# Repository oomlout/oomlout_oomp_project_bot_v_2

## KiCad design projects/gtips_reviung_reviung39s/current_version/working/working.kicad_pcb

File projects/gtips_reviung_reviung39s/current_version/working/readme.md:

# reviung
 
## summary 
* id: gtips_reviung_reviung39s
* user: gtips
* name: reviung
* board: reviung39s
* repo: https://github.com/gtips/reviung
* src_file_repo_kicad_pcb: reviung39s/pcb/reviung39s.kicad_pcb
* src_file_repo_kicad_pcb_link: https://github.com/gtips/reviung/tree/master/reviung39s/pcb/reviung39s.kicad_pcb

* src_file_repo_sch: reviung39s/pcb/reviung39s.sch
* src_file_repo_sch_link: https://github.com/gtips/reviung/tree/master/reviung39s/pcb/reviung39s.sch
* full details link: https://github.com/oomlout/oomlout_oomp_project_bot_v_2/tree/main/projects/gtips_reviung_reviung39s/current_version/working  

## schematic  
  
[schematic (pdf)](working_schematic.pdf) 

## pcb  

[board (pdf)](working.pdf)  

## working_bom
| Id | Designator | Footprint | Quantity | Designation | Supplier and ref |  | None | 
| --- | --- | --- | --- | --- | --- | --- | --- | 
| 1 | U1 | ProMicro | 1 | ProMicro |  |  | [''] | 
| 2 | D1,D2,D3,D4,D5,D6,D7,D8,D9,D10,D11,D12,D13,D14,D15,D16,D17,D18,D19,D20,D21,D22,D23,D24,D25,D26,D27,D28,D29,D30,D31,D32,D33,D34,D35,D36,D37,D38,D39 | D3_TH | 39 | D |  |  | [''] | 
| 3 | SW1,SW2,SW3,SW4,SW5,SW6,SW7,SW8,SW9,SW10,SW11,SW12,SW13,SW14,SW15,SW16,SW17,SW18,SW19,SW20,SW21,SW22,SW23,SW24,SW25,SW26,SW27,SW28,SW29,SW30,SW31,SW32,SW33,SW34,SW35,SW36,SW37,SW39 | MXOnly-1U-NoLED | 38 | SW_PUSH |  |  | [''] | 
| 4 | SW38 | MXOnly-2.25U-ReversedStabilizers-NoLED | 1 | SW_2U_PUSH |  |  | [''] | 
| 5 | G*** | REVIUNG39s-FS-logo | 1 | LOGO |  |  | [''] | 
| 6 | RESET1 | ResetSW_1side | 1 | SW_PUSH |  |  | [''] | 
| 7 | J1 | StripLED_1side | 1 | Conn_01x03_Shielded |  |  | [''] | 
| 8 | G*** | REVIUNG39s-B-logo | 1 | LOGO |  |  | [''] | 

## bom_schematic
| Ref | Qnty | Value | Cmp name | Footprint | Description | Vendor | DNP | 
| --- | --- | --- | --- | --- | --- | --- | --- | 
| D1, D2, D3, D4, D5, D6, D7, D8, D9, D10, D11, D12, D13, D14, D15, D16, D17, D18, D19, D20, D21, D22, D23, D24, D25, D26, D27, D28, D29, D30, D31, D32, D33, D34, D35, D36, D37, D38, D39 | 39 | D | D | _reviung-kbd:D3_TH | Diode |  |  | 
| J1 | 1 | Conn_01x03_Shielded | Conn_01x03 | _reviung-kbd:StripLED_1side | Generic connector, single row, 01x03, script generated (kicad-library-utils/schlib/autogen/connector/) |  |  | 
| RESET1 | 1 | SW_PUSH | SW_PUSH-_reviung-kbd | _reviung-kbd:ResetSW_1side |  |  |  | 
| SW1, SW2, SW3, SW4, SW5, SW6, SW7, SW8, SW9, SW10, SW11, SW12, SW13, SW14, SW15, SW16, SW17, SW18, SW19, SW20, SW21, SW22, SW23, SW24, SW25, SW26, SW27, SW28, SW29, SW30, SW31, SW32, SW33, SW34, SW35, SW36, SW37, SW39 | 38 | SW_PUSH | SW_PUSH-_reviung-kbd | _reviung-kbd:MXOnly-1U-NoLED |  |  |  | 
| SW38 | 1 | SW_2U_PUSH | SW_PUSH-_reviung-kbd | _reviung-kbd:MXOnly-2.25U-ReversedStabilizers-NoLED |  |  |  | 
| U1 | 1 | ProMicro | ProMicro-_reviung-kbd | _reviung-kbd:ProMicro |  |  |  |

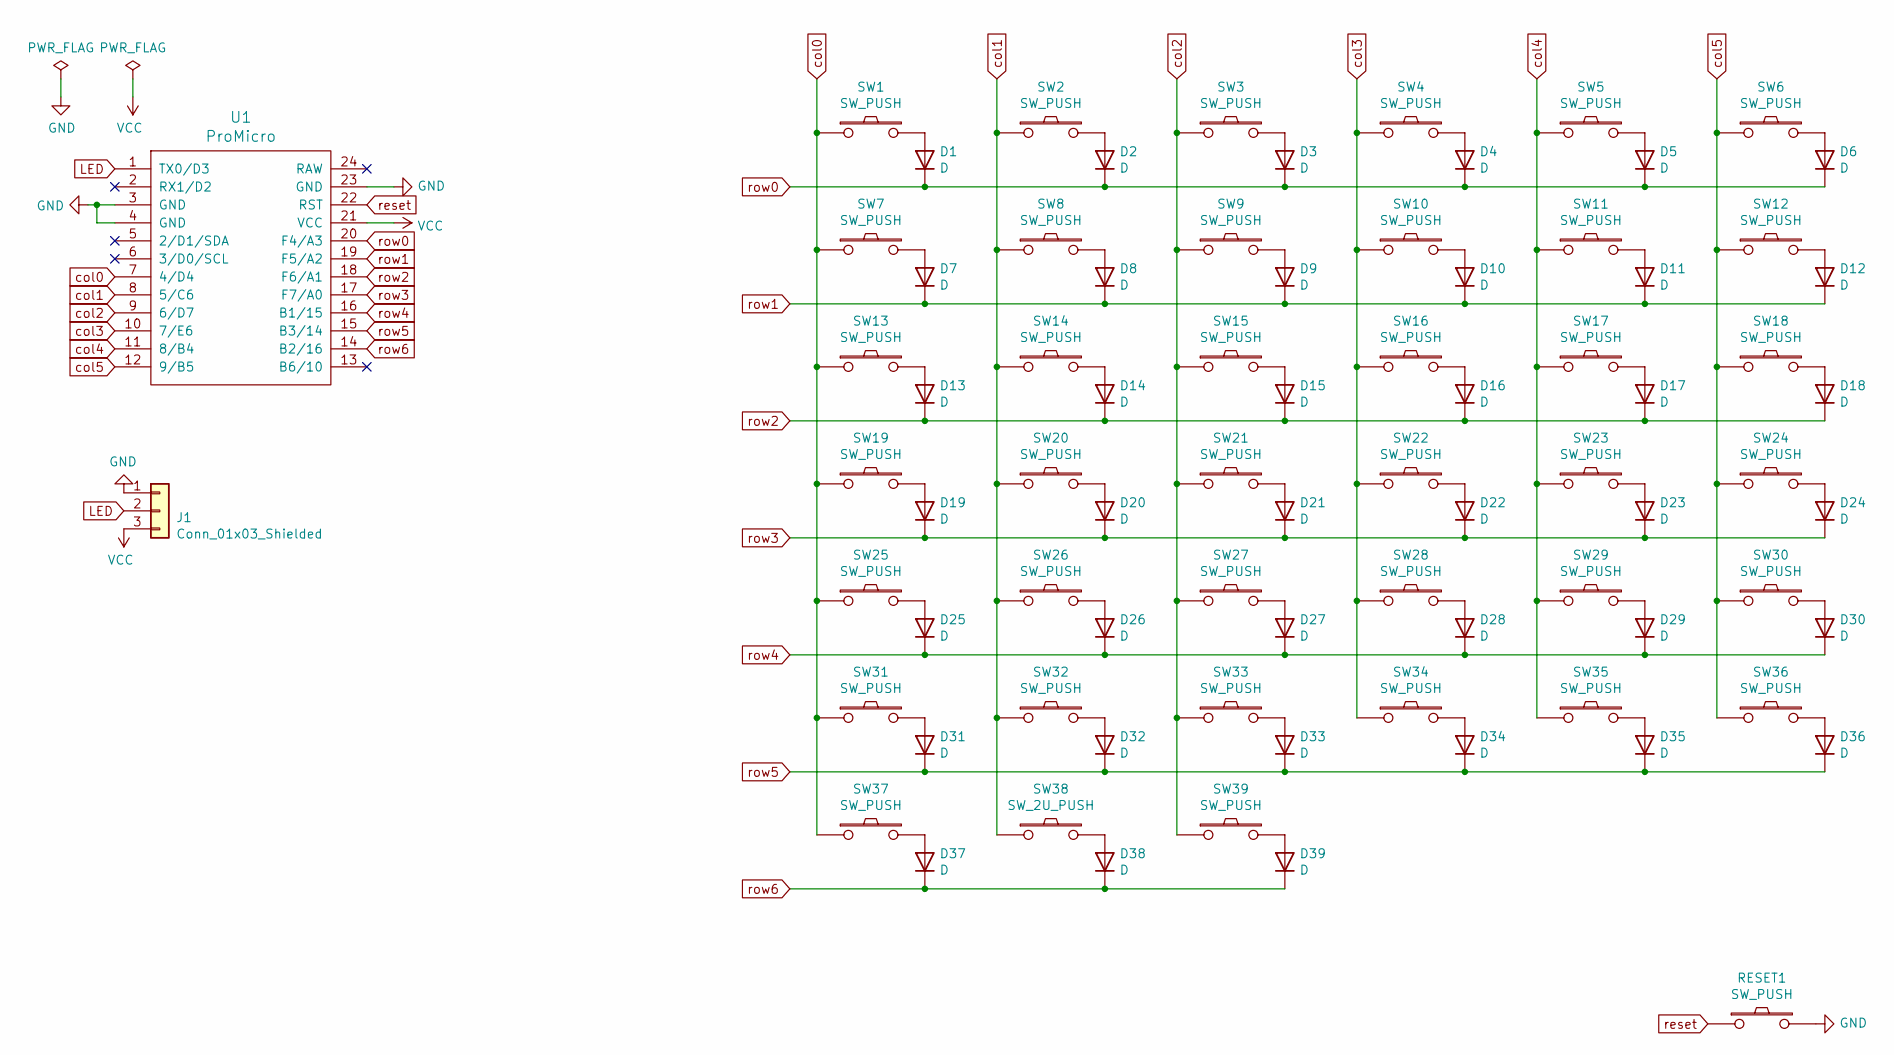
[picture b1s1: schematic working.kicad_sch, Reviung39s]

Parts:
D1, D2, D3, D4, D5, D6, D7, D8, D9, D10, D11, D12, D13, D14, D15, D16, D17, D18, D19, D20, D21, D22, D23, D24, D25, D26, D27, D28, D29, D30, D31, D32, D33, D34, D35, D36, D37, D38, D39: D; D3_TH
J1: Conn_01x03_Shielded; StripLED_1side
RESET1: SW_PUSH; ResetSW_1side
SW1, SW2, SW3, SW4, SW5, SW6, SW7, SW8, SW9, SW10, SW11, SW12, SW13, SW14, SW15, SW16, SW17, SW18, SW19, SW20, SW21, SW22, SW23, SW24, SW25, SW26, SW27, SW28, SW29, SW30, SW31, SW32, SW33, SW34, SW35, SW36, SW37, SW39: SW_PUSH; MXOnly-1U-NoLED
SW38: SW_2U_PUSH; MXOnly-2.25U-ReversedStabilizers-NoLED
U1: ProMicro

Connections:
GND: J1.1, RESET1.2, U1.3 (GND), U1.4 (GND), U1.23 (GND)
LED: J1.2, U1.1 (TX0/D3)
unnamed: D1.2 (A), SW1.2
unnamed: D2.2 (A), SW2.2
unnamed: D3.2 (A), SW3.2
unnamed: D4.2 (A), SW4.2
unnamed: D5.2 (A), SW5.2
unnamed: D6.2 (A), SW6.2
unnamed: D7.2 (A), SW7.2
unnamed: D8.2 (A), SW8.2
unnamed: D9.2 (A), SW9.2
unnamed: D10.2 (A), SW10.2
unnamed: D11.2 (A), SW11.2
unnamed: D12.2 (A), SW12.2
unnamed: D13.2 (A), SW13.2
unnamed: D14.2 (A), SW14.2
unnamed: D15.2 (A), SW15.2
unnamed: D16.2 (A), SW16.2
unnamed: D17.2 (A), SW17.2
unnamed: D18.2 (A), SW18.2
unnamed: D19.2 (A), SW19.2
unnamed: D20.2 (A), SW20.2
unnamed: D21.2 (A), SW21.2
unnamed: D22.2 (A), SW22.2
unnamed: D23.2 (A), SW23.2
unnamed: D24.2 (A), SW24.2
unnamed: D25.2 (A), SW25.2
unnamed: D26.2 (A), SW26.2
unnamed: D27.2 (A), SW27.2
unnamed: D28.2 (A), SW28.2
unnamed: D29.2 (A), SW29.2
unnamed: D30.2 (A), SW30.2
unnamed: D31.2 (A), SW31.2
unnamed: D32.2 (A), SW32.2
unnamed: D33.2 (A), SW33.2
unnamed: D34.2 (A), SW34.2
unnamed: D35.2 (A), SW35.2
unnamed: D36.2 (A), SW36.2
unnamed: D37.2 (A), SW37.2
unnamed: D38.2 (A), SW38.2
unnamed: D39.2 (A), SW39.2
VCC: J1.3, U1.21 (VCC)
col0: SW1.1, SW7.1, SW13.1, SW19.1, SW25.1, SW31.1, SW37.1, U1.7 (4/D4)
col1: SW2.1, SW8.1, SW14.1, SW20.1, SW26.1, SW32.1, SW38.1, U1.8 (5/C6)
col2: SW3.1, SW9.1, SW15.1, SW21.1, SW27.1, SW33.1, SW39.1, U1.9 (6/D7)
col3: SW4.1, SW10.1, SW16.1, SW22.1, SW28.1, SW34.1, U1.10 (7/E6)
col4: SW5.1, SW11.1, SW17.1, SW23.1, SW29.1, SW35.1, U1.11 (8/B4)
col5: SW6.1, SW12.1, SW18.1, SW24.1, SW30.1, SW36.1, U1.12 (9/B5)
reset: RESET1.1, U1.22 (RST)
row0: D1.1 (K), D2.1 (K), D3.1 (K), D4.1 (K), D5.1 (K), D6.1 (K), U1.20 (F4/A3)
row1: D7.1 (K), D8.1 (K), D9.1 (K), D10.1 (K), D11.1 (K), D12.1 (K), U1.19 (F5/A2)
row2: D13.1 (K), D14.1 (K), D15.1 (K), D16.1 (K), D17.1 (K), D18.1 (K), U1.18 (F6/A1)
row3: D19.1 (K), D20.1 (K), D21.1 (K), D22.1 (K), D23.1 (K), D24.1 (K), U1.17 (F7/A0)
row4: D25.1 (K), D26.1 (K), D27.1 (K), D28.1 (K), D29.1 (K), D30.1 (K), U1.16 (B1/15)
row5: D31.1 (K), D32.1 (K), D33.1 (K), D34.1 (K), D35.1 (K), D36.1 (K), U1.15 (B3/14)
row6: D37.1 (K), D38.1 (K), D39.1 (K), U1.14 (B2/16)

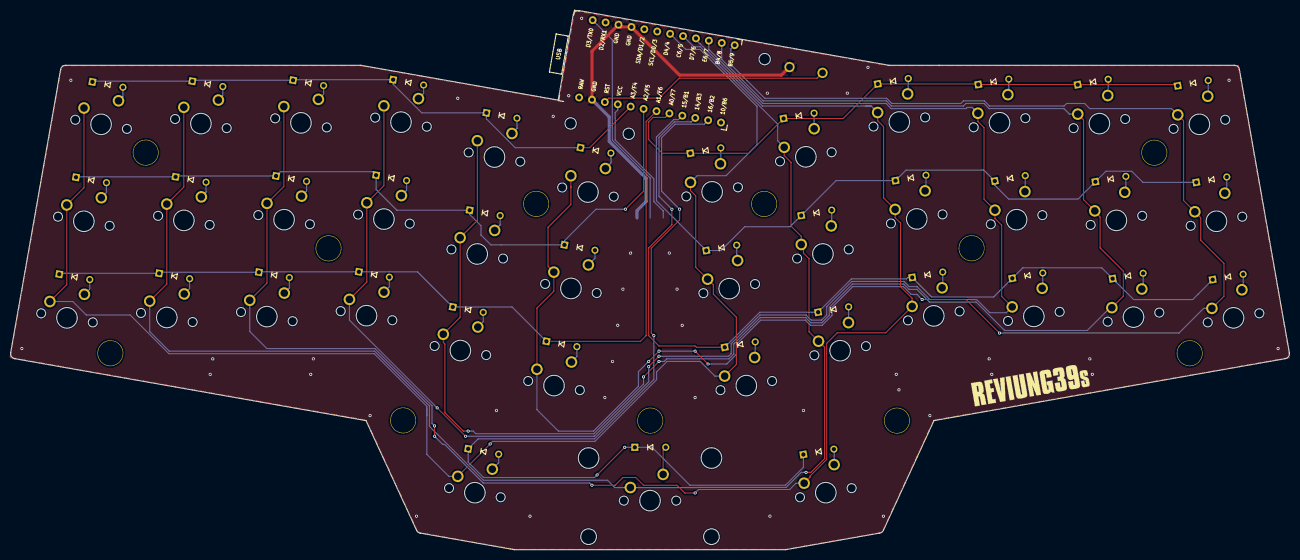
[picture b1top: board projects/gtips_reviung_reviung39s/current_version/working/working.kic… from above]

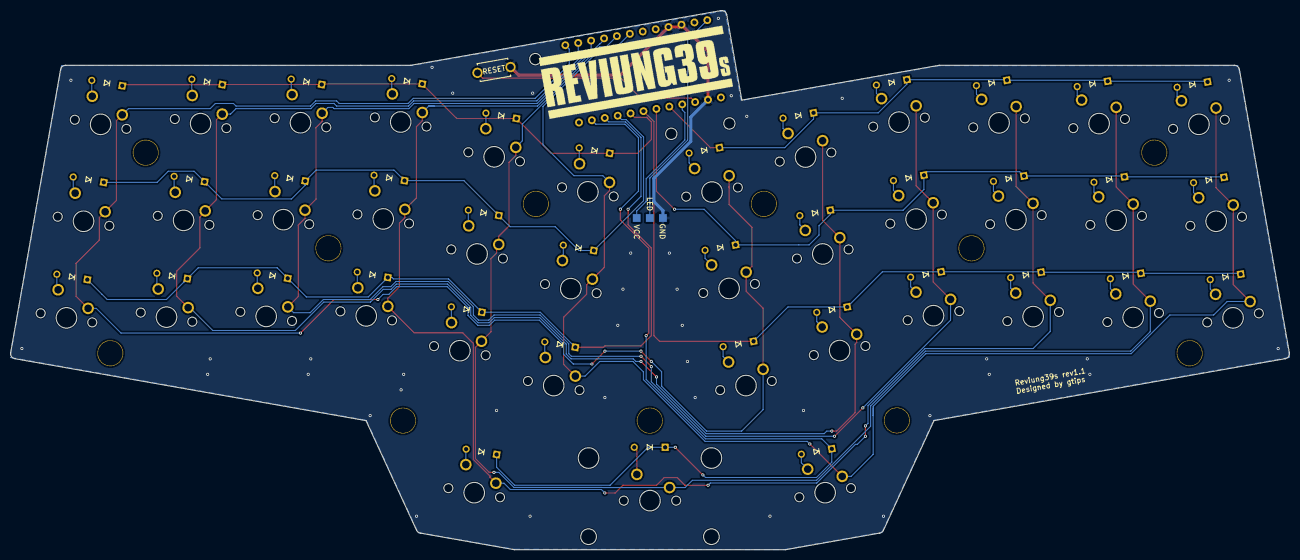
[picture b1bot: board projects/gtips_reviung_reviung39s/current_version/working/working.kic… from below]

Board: 2 copper layers, 247.9 x 104.5 mm, 92 parts (2 on the bottom side), 56 nets.

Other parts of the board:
H1: H1; HOLE
H2: H2; HOLE
H3: H3; HOLE
H4: H4; HOLE
H5: H5; HOLE
H6: H6; HOLE
H7: H7; HOLE
H8: H8; HOLE
H9: H9; HOLE
H10: H10; HOLE
H11: H11; HOLE

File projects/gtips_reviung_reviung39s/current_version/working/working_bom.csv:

"Id";"Designator";"Footprint";"Quantity";"Designation";"Supplier and ref";
1;"U1";"ProMicro";1;"ProMicro";;;
2;"D1,D2,D3,D4,D5,D6,D7,D8,D9,D10,D11,D12,D13,D14,D15,D16,D17,D18,D19,D20,D21,D22,D23,D24,D25,D26,D27,D28,D29,D30,D31,D32,D33,D34,D35,D36,D37,D38,D39";"D3_TH";39;"D";;;
3;"SW1,SW2,SW3,SW4,SW5,SW6,SW7,SW8,SW9,SW10,SW11,SW12,SW13,SW14,SW15,SW16,SW17,SW18,SW19,SW20,SW21,SW22,SW23,SW24,SW25,SW26,SW27,SW28,SW29,SW30,SW31,SW32,SW33,SW34,SW35,SW36,SW37,SW39";"MXOnly-1U-NoLED";38;"SW_PUSH";;;
4;"SW38";"MXOnly-2.25U-ReversedStabilizers-NoLED";1;"SW_2U_PUSH";;;
5;"G***";"REVIUNG39s-FS-logo";1;"LOGO";;;
6;"RESET1";"ResetSW_1side";1;"SW_PUSH";;;
7;"J1";"StripLED_1side";1;"Conn_01x03_Shielded";;;
8;"G***";"REVIUNG39s-B-logo";1;"LOGO";;;

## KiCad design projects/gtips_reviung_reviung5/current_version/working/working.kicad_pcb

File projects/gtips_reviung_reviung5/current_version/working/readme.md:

# reviung
 
## summary 
* id: gtips_reviung_reviung5
* user: gtips
* name: reviung
* board: reviung5
* repo: https://github.com/gtips/reviung
* src_file_repo_kicad_pcb: reviung5/pcb/ver1.0/reviung5.kicad_pcb
* src_file_repo_kicad_pcb_link: https://github.com/gtips/reviung/tree/master/reviung5/pcb/ver1.0/reviung5.kicad_pcb

* src_file_repo_sch: reviung5/pcb/ver1.0/reviung5.sch
* src_file_repo_sch_link: https://github.com/gtips/reviung/tree/master/reviung5/pcb/ver1.0/reviung5.sch
* full details link: https://github.com/oomlout/oomlout_oomp_project_bot_v_2/tree/main/projects/gtips_reviung_reviung5/current_version/working  

## schematic  
  
[schematic (pdf)](working_schematic.pdf) 

## pcb  

[board (pdf)](working.pdf)  

## working_bom
| Id | Designator | Footprint | Quantity | Designation | Supplier and ref |  | None | 
| --- | --- | --- | --- | --- | --- | --- | --- | 
| 1 | RESW1,RESW2 | RotaryEncoder_Alps_EC12E-Switch_Vertical_H20mm_CircularMountingHoles | 2 | Rotary_Encoder_Switch |  |  | [''] | 
| 2 | SW1,SW5 | MXOnly-1U-3pin | 2 | SW_PUSH |  |  | [''] | 
| 3 | SW2,SW3,SW4 | MXOnly-1U-NoLED | 3 | SW_PUSH |  |  | [''] | 
| 4 | U1 | ProMicro | 1 | ProMicro |  |  | [''] | 
| 5 | REF**,REF**,REF** | HOLE_4.2mm | 3 | HOLE_4.2mm |  |  | [''] | 
| 6 | G*** | QMK-x4-ver1 | 1 | LOGO |  |  | [''] | 
| 7 | D1,D2,D3,D4,D5 | D3_TH_SMD_1side | 5 | 1N4148 |  |  | [''] | 
| 8 | reset1 | ResetSW_TH_SMD | 1 | SW_PUSH |  |  | [''] | 
| 9 | RGB1,RGB2,RGB3,RGB4 | LED_WS2812B_PLCC4_5.0x5.0mm_P3.2mm | 4 | WS2812B |  |  | [''] | 
| 10 | G*** | reviung-logo | 1 | LOGO |  |  | [''] | 

## bom_schematic
| Ref | Qnty | Value | Cmp name | Footprint | Description | Vendor | DNP | 
| --- | --- | --- | --- | --- | --- | --- | --- | 
| D1, D2, D3, D4, D5 | 5 | 1N4148 | 1N4148 | _reviung-kbd:D3_TH_SMD_1side | 100V 0.15A standard switching diode, DO-35 |  |  | 
| reset1 | 1 | SW_PUSH | SW_PUSH-_reviung-kbd | _reviung-kbd:ResetSW_TH_SMD |  |  |  | 
| RESW1, RESW2 | 2 | Rotary_Encoder_Switch | Rotary_Encoder_Switch-Device | Rotary_Encoder:RotaryEncoder_Alps_EC12E-Switch_Vertical_H20mm_CircularMountingHoles |  |  |  | 
| RGB1, RGB2, RGB3, RGB4 | 4 | WS2812B | WS2812B | _reviung-kbd:LED_WS2812B_PLCC4_5.0x5.0mm_P3.2mm | RGB LED with integrated controller |  |  | 
| SW1, SW5 | 2 | SW_PUSH | SW_PUSH-_reviung-kbd | _reviung-kbd:MXOnly-1U-3pin |  |  |  | 
| SW2, SW3, SW4 | 3 | SW_PUSH | SW_PUSH-_reviung-kbd | _reviung-kbd:MXOnly-1U-NoLED |  |  |  | 
| U1 | 1 | ProMicro | ProMicro-_reviung-kbd | _reviung-kbd:ProMicro |  |  |  | 

## mounting_holes
| x | y | package | value | ref | size | 
| --- | --- | --- | --- | --- | --- | 
| 0.0 | 0.86 | RotaryEncoder_Alps_EC12E-Switch_Vertical_H20mm_CircularMountingHoles | Rotary_Encoder_Switch | RESW1 | m3 | 
| 78.94 | 0.0 | RotaryEncoder_Alps_EC12E-Switch_Vertical_H20mm_CircularMountingHoles | Rotary_Encoder_Switch | RESW2 | m3 |

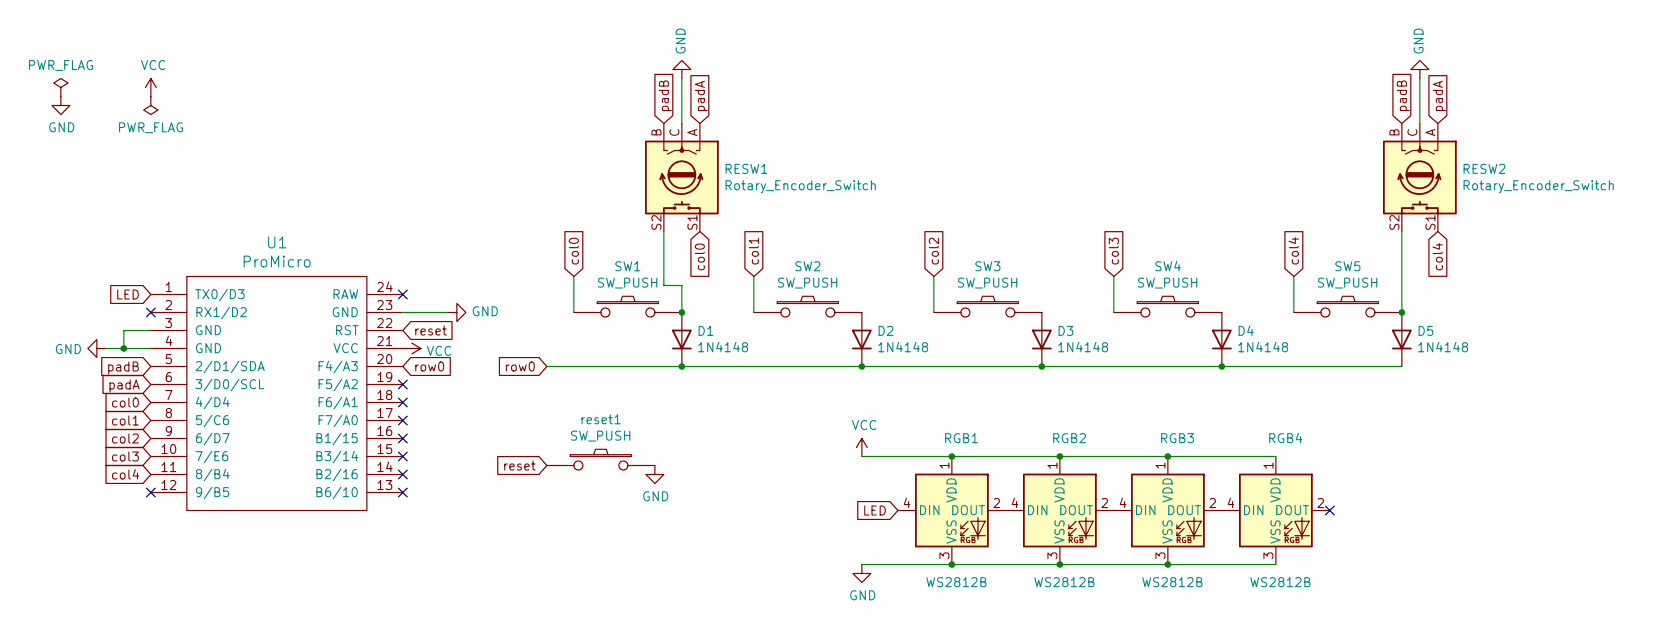
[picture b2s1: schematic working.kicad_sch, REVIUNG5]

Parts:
D1, D2, D3, D4, D5: 1N4148; D3_TH_SMD_1side
RESW1, RESW2: Rotary_Encoder_Switch; RotaryEncoder_Alps_EC12E-Switch_Vertical_H20mm_CircularMoun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
RGB1, RGB2, RGB3, RGB4: WS2812B; LED_WS2812B_PLCC4_5.0x5.0mm_P3.2mm
SW1, SW5: SW_PUSH; MXOnly-1U-3pin
SW2, SW3, SW4: SW_PUSH; MXOnly-1U-NoLED
U1: ProMicro
reset1: SW_PUSH; ResetSW_TH_SMD

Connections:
GND: RESW1.C, RESW2.C, RGB1.3 (VSS), RGB2.3 (VSS), RGB3.3 (VSS), RGB4.3 (VSS), U1.3 (GND), U1.4 (GND), U1.23 (GND), reset1.2
LED: RGB1.4 (DIN), U1.1 (TX0/D3)
unnamed: D1.2 (A), RESW1.S2, SW1.2
unnamed: D2.2 (A), SW2.2
unnamed: D3.2 (A), SW3.2
unnamed: D4.2 (A), SW4.2
unnamed: D5.2 (A), RESW2.S2, SW5.2
unnamed: RGB1.2 (DOUT), RGB2.4 (DIN)
unnamed: RGB2.2 (DOUT), RGB3.4 (DIN)
unnamed: RGB3.2 (DOUT), RGB4.4 (DIN)
VCC: RGB1.1 (VDD), RGB2.1 (VDD), RGB3.1 (VDD), RGB4.1 (VDD), U1.21 (VCC)
col0: RESW1.S1, SW1.1, U1.7 (4/D4)
col1: SW2.1, U1.8 (5/C6)
col2: SW3.1, U1.9 (6/D7)
col3: SW4.1, U1.10 (7/E6)
col4: RESW2.S1, SW5.1, U1.11 (8/B4)
padA: RESW1.A, RESW2.A, U1.6 (3/D0/SCL)
padB: RESW1.B, RESW2.B, U1.5 (2/D1/SDA)
reset: U1.22 (RST), reset1.1
row0: D1.1 (K), D2.1 (K), D3.1 (K), D4.1 (K), D5.1 (K), U1.20 (F4/A3)

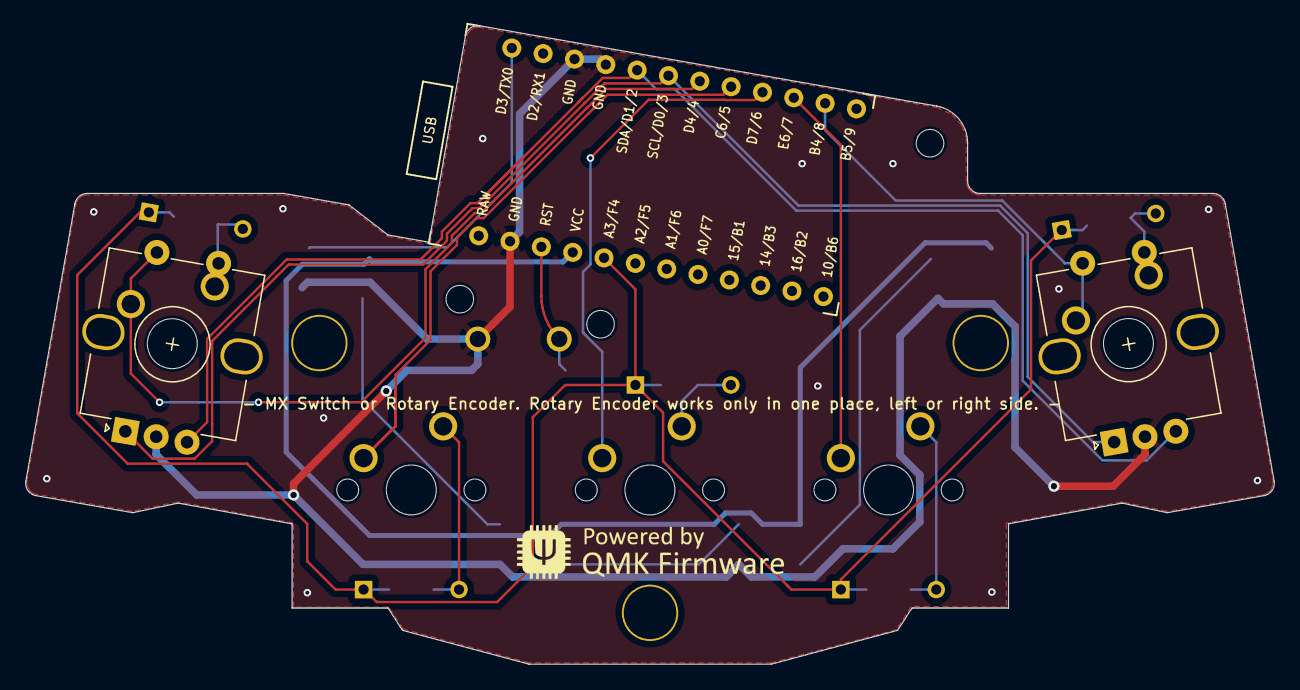
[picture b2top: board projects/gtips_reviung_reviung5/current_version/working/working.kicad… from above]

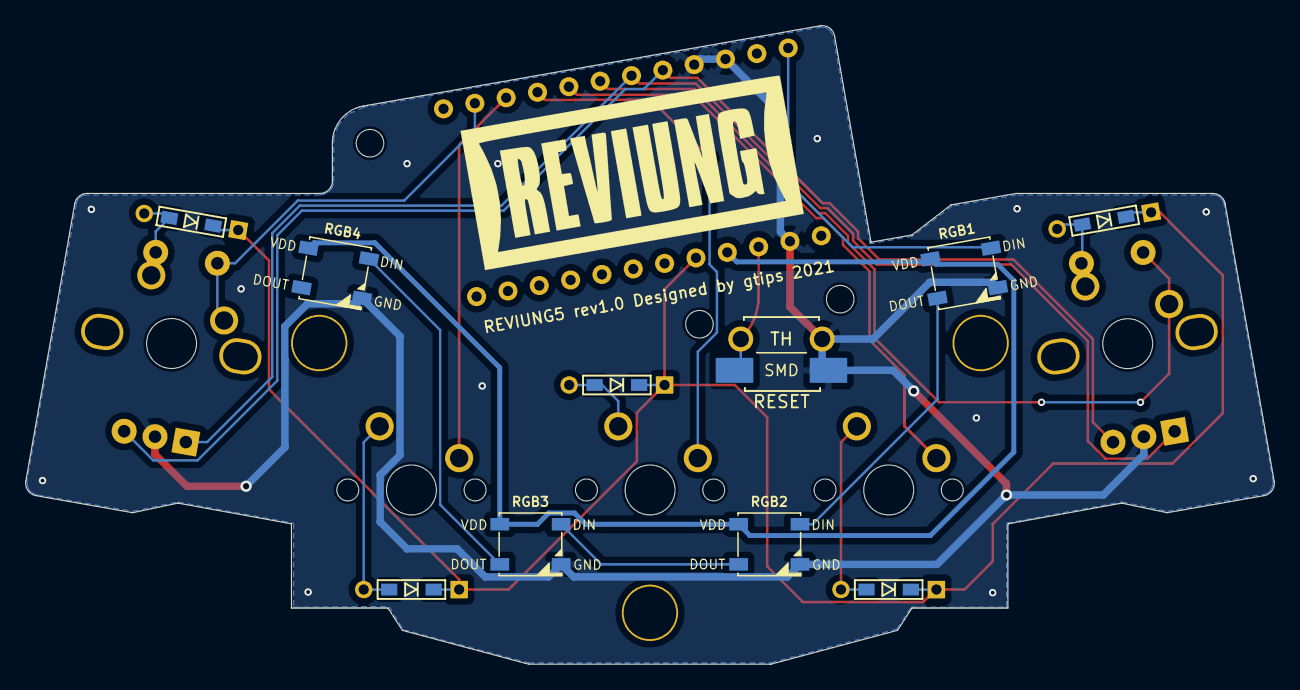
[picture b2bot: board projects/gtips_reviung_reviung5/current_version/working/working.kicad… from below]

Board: 2 copper layers, 99.7 x 51.0 mm, 21 parts (10 on the bottom side), 20 nets.

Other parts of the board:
Ref**: Val**; HOLE_2.2mm
Ref**#2, Ref**#3: Val**; HOLE_2.2mm

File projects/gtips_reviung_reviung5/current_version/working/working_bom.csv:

"Id";"Designator";"Footprint";"Quantity";"Designation";"Supplier and ref";
1;"RESW1,RESW2";"RotaryEncoder_Alps_EC12E-Switch_Vertical_H20mm_CircularMountingHoles";2;"Rotary_Encoder_Switch";;;
2;"SW1,SW5";"MXOnly-1U-3pin";2;"SW_PUSH";;;
3;"SW2,SW3,SW4";"MXOnly-1U-NoLED";3;"SW_PUSH";;;
4;"U1";"ProMicro";1;"ProMicro";;;
5;"REF**,REF**,REF**";"HOLE_4.2mm";3;"HOLE_4.2mm";;;
6;"G***";"QMK-x4-ver1";1;"LOGO";;;
7;"D1,D2,D3,D4,D5";"D3_TH_SMD_1side";5;"1N4148";;;
8;"reset1";"ResetSW_TH_SMD";1;"SW_PUSH";;;
9;"RGB1,RGB2,RGB3,RGB4";"LED_WS2812B_PLCC4_5.0x5.0mm_P3.2mm";4;"WS2812B";;;
10;"G***";"reviung-logo";1;"LOGO";;;

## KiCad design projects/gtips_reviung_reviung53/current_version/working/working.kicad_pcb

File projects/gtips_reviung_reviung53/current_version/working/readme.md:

# reviung
 
## summary 
* id: gtips_reviung_reviung53
* user: gtips
* name: reviung
* board: reviung53
* repo: https://github.com/gtips/reviung
* src_file_repo_kicad_pcb: reviung53/pcb/main-pcb/reviung53-ver1.0/reviung53.kicad_pcb
* src_file_repo_kicad_pcb_link: https://github.com/gtips/reviung/tree/master/reviung53/pcb/main-pcb/reviung53-ver1.0/reviung53.kicad_pcb

* src_file_repo_sch: reviung53/pcb/main-pcb/reviung53-ver1.0/reviung53.sch
* src_file_repo_sch_link: https://github.com/gtips/reviung/tree/master/reviung53/pcb/main-pcb/reviung53-ver1.0/reviung53.sch
* full details link: https://github.com/oomlout/oomlout_oomp_project_bot_v_2/tree/main/projects/gtips_reviung_reviung53/current_version/working  

## schematic  
  
[schematic (pdf)](working_schematic.pdf) 

## pcb  

[board (pdf)](working.pdf)  

## working_bom
| Id | Designator | Footprint | Quantity | Designation | Supplier and ref |  | None | 
| --- | --- | --- | --- | --- | --- | --- | --- | 
| 1 | SW1 | MXOnly-1U-Hotswap | 1 | 1 |  |  | [''] | 
| 2 | SW2 | MXOnly-1U-Hotswap | 1 | 2 |  |  | [''] | 
| 3 | SW3 | MXOnly-1U-Hotswap | 1 | 3 |  |  | [''] | 
| 4 | SW4 | MXOnly-1U-Hotswap | 1 | 4 |  |  | [''] | 
| 5 | SW5 | MXOnly-1U-Hotswap | 1 | 5 |  |  | [''] | 
| 6 | SW6 | MXOnly-1U-Hotswap | 1 | 6 |  |  | [''] | 
| 7 | SW7,SW39,SW49,SW57 | MXOnly-1.5U-Hotswap | 4 | 1.5U |  |  | [''] | 
| 8 | SW8 | MXOnly-1U-Hotswap | 1 | Q |  |  | [''] | 
| 9 | SW9 | MXOnly-1U-Hotswap | 1 | W |  |  | [''] | 
| 10 | SW10 | MXOnly-1U-Hotswap | 1 | E |  |  | [''] | 
| 11 | SW11 | MXOnly-1U-Hotswap | 1 | R |  |  | [''] | 
| 12 | SW12 | MXOnly-1U-Hotswap | 1 | T |  |  | [''] | 
| 13 | SW13 | MXOnly-1U-Hotswap | 1 | Y |  |  | [''] | 
| 14 | SW14 | MXOnly-1U-Hotswap | 1 | U |  |  | [''] | 
| 15 | SW16,SW48 | MXOnly-1.75U-Hotswap | 2 | 1.75U |  |  | [''] | 
| 16 | SW17 | MXOnly-1U-Hotswap | 1 | A |  |  | [''] | 
| 17 | SW18 | MXOnly-1U-Hotswap | 1 | S |  |  | [''] | 
| 18 | SW19 | MXOnly-1U-Hotswap | 1 | D |  |  | [''] | 
| 19 | SW20 | MXOnly-1U-Hotswap | 1 | F |  |  | [''] | 
| 20 | SW21 | MXOnly-1U-Hotswap | 1 | G |  |  | [''] | 
| 21 | SW22 | MXOnly-1U-Hotswap | 1 | H |  |  | [''] | 
| 22 | SW23 | MXOnly-1U-Hotswap | 1 | J |  |  | [''] | 
| 23 | SW24,SW43 | MXOnly-2.25U-Hotswap-ReversedStabilizers | 2 | 2.25U |  |  | [''] | 
| 24 | SW25 | MXOnly-1U-Hotswap | 1 | Z |  |  | [''] | 
| 25 | SW26 | MXOnly-1U-Hotswap | 1 | X |  |  | [''] | 
| 26 | SW27 | MXOnly-1U-Hotswap | 1 | C |  |  | [''] | 
| 27 | SW28 | MXOnly-1U-Hotswap | 1 | V |  |  | [''] | 
| 28 | SW29 | MXOnly-1U-Hotswap | 1 | B |  |  | [''] | 
| 29 | SW30 | MXOnly-1U-Hotswap | 1 | N |  |  | [''] | 
| 30 | SW31 | MXOnly-1U-Hotswap | 1 | M |  |  | [''] | 
| 31 | SW32 | MXOnly-1U-Hotswap | 1 | 7 |  |  | [''] | 
| 32 | SW33 | MXOnly-1U-Hotswap | 1 | 8 |  |  | [''] | 
| 33 | SW34 | MXOnly-1U-Hotswap | 1 | 9 |  |  | [''] | 
| 34 | SW35,SW37 | MXOnly-1U-Hotswap | 2 | 0 |  |  | [''] | 
| 35 | SW36 | MXOnly-1U-Hotswap | 1 | I |  |  | [''] | 
| 36 | SW38 | MXOnly-1U-Hotswap | 1 | P |  |  | [''] | 
| 37 | SW40 | MXOnly-1U-Hotswap | 1 | K |  |  | [''] | 
| 38 | SW41 | MXOnly-1U-Hotswap | 1 | L |  |  | [''] | 
| 39 | SW42,SW46 | MXOnly-1U-Hotswap | 2 | 1U |  |  | [''] | 
| 40 | SW44,SW50,SW51,SW55,SW56,SW15 | MXOnly-1.25U-Hotswap | 6 | 1.25U |  |  | [''] | 
| 41 | SW53 | MXOnly-6.25U-Hotswap-ReversedStabilizers | 1 | 6.25U |  |  | [''] | 
| 42 | SW54 | MXOnly-2.25U-Hotswap | 1 | 2.25U |  |  | [''] | 
| 43 | U1 | ProMicro | 1 | ProMicro |  |  | [''] | 
| 44 | SW52 | MXOnly-2.75U-Hotswap | 1 | 2.75U |  |  | [''] | 
| 45 | SW45 | MXOnly-1U-Hotswap | 1 | < |  |  | [''] | 
| 46 | REF**,REF**,REF**,REF**,REF**,REF**,REF**,REF**,REF**,REF**,REF** | HOLE_4.2mm | 11 | HOLE_4.2mm |  |  | [''] | 
| 47 | breakaway,breakaway,breakaway,breakaway,breakaway,breakaway | Stamp_Holes_7.5mm | 6 | Stamp_Holes_7.5mm |  |  | [''] | 
| 48 | SW47 | MXOnly-2.75U-Hotswap-ReversedStabilizers | 1 | 2.75U |  |  | [''] | 
| 49 | D1,D2,D3,D4,D5,D6,D7,D8,D9,D10,D11,D12,D13,D14,D15,D16,D17,D18,D19,D20,D21,D22,D23,D24,D25,D26,D27,D28,D29,D30,D31,D32,D33,D34,D35,D36,D37,D38,D39,D40,D41,D42,D43,D44,D45,D46,D47,D48,D49,D50,D51,D52,D53 | D3_SMD_1side | 53 | 1N4148W |  |  | [''] | 
| 50 | RESET1 | ResetSW_1side | 1 | SW_PUSH |  |  | [''] | 
| 51 | RGB1,RGB2,RGB3,RGB4,RGB5,RGB6,RGB7,RGB8,RGB9,RGB10 | LED_WS2812B_PLCC4_5.0x5.0mm_P3.2mm_BigFoot | 10 | WS2812B |  |  | [''] | 
| 52 | G*** | reviung-logo | 1 | LOGO |  |  | [''] | 
| 53 | G*** | QMK-x4-ver1 | 1 | LOGO |  |  | [''] | 

## bom_schematic
| Ref | Qnty | Value | Cmp name | Footprint | Description | Vendor | DNP | 
| --- | --- | --- | --- | --- | --- | --- | --- | 
| D1, D2, D3, D4, D5, D6, D7, D8, D9, D10, D11, D12, D13, D14, D15, D16, D17, D18, D19, D20, D21, D22, D23, D24, D25, D26, D27, D28, D29, D30, D31, D32, D33, D34, D35, D36, D37, D38, D39, D40, D41, D42, D43, D44, D45, D46, D47, D48, D49, D50, D51, D52, D53 | 53 | 1N4148W | 1N4148W | _reviung-kbd:D3_SMD_1side | 75V 0.15A Fast Switching Diode, SOD-123 |  |  | 
| RESET1 | 1 | SW_PUSH | SW_PUSH-_reviung-kbd | _reviung-kbd:ResetSW_1side |  |  |  | 
| RGB1, RGB2, RGB3, RGB4, RGB5, RGB6, RGB7, RGB8, RGB9, RGB10 | 10 | WS2812B | WS2812B | _reviung-kbd:LED_WS2812B_PLCC4_5.0x5.0mm_P3.2mm_BigFoot | RGB LED with integrated controller |  |  | 
| SW1 | 1 | 1 | SW_PUSH-_reviung-kbd | _reviung-kbd:MXOnly-1U-Hotswap |  |  |  | 
| SW2 | 1 | 2 | SW_PUSH-_reviung-kbd | _reviung-kbd:MXOnly-1U-Hotswap |  |  |  | 
| SW3 | 1 | 3 | SW_PUSH-_reviung-kbd | _reviung-kbd:MXOnly-1U-Hotswap |  |  |  | 
| SW4 | 1 | 4 | SW_PUSH-_reviung-kbd | _reviung-kbd:MXOnly-1U-Hotswap |  |  |  | 
| SW5 | 1 | 5 | SW_PUSH-_reviung-kbd | _reviung-kbd:MXOnly-1U-Hotswap |  |  |  | 
| SW6 | 1 | 6 | SW_PUSH-_reviung-kbd | _reviung-kbd:MXOnly-1U-Hotswap |  |  |  | 
| SW7, SW39, SW49, SW57 | 4 | 1.5U | SW_PUSH-_reviung-kbd | _reviung-kbd:MXOnly-1.5U-Hotswap |  |  |  | 
| SW8 | 1 | Q | SW_PUSH-_reviung-kbd | _reviung-kbd:MXOnly-1U-Hotswap |  |  |  | 
| SW9 | 1 | W | SW_PUSH-_reviung-kbd | _reviung-kbd:MXOnly-1U-Hotswap |  |  |  | 
| SW10 | 1 | E | SW_PUSH-_reviung-kbd | _reviung-kbd:MXOnly-1U-Hotswap |  |  |  | 
| SW11 | 1 | R | SW_PUSH-_reviung-kbd | _reviung-kbd:MXOnly-1U-Hotswap |  |  |  | 
| SW12 | 1 | T | SW_PUSH-_reviung-kbd | _reviung-kbd:MXOnly-1U-Hotswap |  |  |  | 
| SW13 | 1 | Y | SW_PUSH-_reviung-kbd | _reviung-kbd:MXOnly-1U-Hotswap |  |  |  | 
| SW14 | 1 | U | SW_PUSH-_reviung-kbd | _reviung-kbd:MXOnly-1U-Hotswap |  |  |  | 
| SW15, SW44, SW50, SW51, SW55, SW56 | 6 | 1.25U | SW_PUSH-_reviung-kbd | _reviung-kbd:MXOnly-1.25U-Hotswap |  |  |  | 
| SW16, SW48 | 2 | 1.75U | SW_PUSH-_reviung-kbd | _reviung-kbd:MXOnly-1.75U-Hotswap |  |  |  | 
| SW17 | 1 | A | SW_PUSH-_reviung-kbd | _reviung-kbd:MXOnly-1U-Hotswap |  |  |  | 
| SW18 | 1 | S | SW_PUSH-_reviung-kbd | _reviung-kbd:MXOnly-1U-Hotswap |  |  |  | 
| SW19 | 1 | D | SW_PUSH-_reviung-kbd | _reviung-kbd:MXOnly-1U-Hotswap |  |  |  | 
| SW20 | 1 | F | SW_PUSH-_reviung-kbd | _reviung-kbd:MXOnly-1U-Hotswap |  |  |  | 
| SW21 | 1 | G | SW_PUSH-_reviung-kbd | _reviung-kbd:MXOnly-1U-Hotswap |  |  |  | 
| SW22 | 1 | H | SW_PUSH-_reviung-kbd | _reviung-kbd:MXOnly-1U-Hotswap |  |  |  | 
| SW23 | 1 | J | SW_PUSH-_reviung-kbd | _reviung-kbd:MXOnly-1U-Hotswap |  |  |  | 
| SW24, SW43 | 2 | 2.25U | SW_PUSH-_reviung-kbd | _reviung-kbd:MXOnly-2.25U-Hotswap-ReversedStabilizers |  |  |  | 
| SW25 | 1 | Z | SW_PUSH-_reviung-kbd | _reviung-kbd:MXOnly-1U-Hotswap |  |  |  | 
| SW26 | 1 | X | SW_PUSH-_reviung-kbd | _reviung-kbd:MXOnly-1U-Hotswap |  |  |  | 
| SW27 | 1 | C | SW_PUSH-_reviung-kbd | _reviung-kbd:MXOnly-1U-Hotswap |  |  |  | 
| SW28 | 1 | V | SW_PUSH-_reviung-kbd | _reviung-kbd:MXOnly-1U-Hotswap |  |  |  | 
| SW29 | 1 | B | SW_PUSH-_reviung-kbd | _reviung-kbd:MXOnly-1U-Hotswap |  |  |  | 
| SW30 | 1 | N | SW_PUSH-_reviung-kbd | _reviung-kbd:MXOnly-1U-Hotswap |  |  |  | 
| SW31 | 1 | M | SW_PUSH-_reviung-kbd | _reviung-kbd:MXOnly-1U-Hotswap |  |  |  | 
| SW32 | 1 | 7 | SW_PUSH-_reviung-kbd | _reviung-kbd:MXOnly-1U-Hotswap |  |  |  | 
| SW33 | 1 | 8 | SW_PUSH-_reviung-kbd | _reviung-kbd:MXOnly-1U-Hotswap |  |  |  | 
| SW34 | 1 | 9 | SW_PUSH-_reviung-kbd | _reviung-kbd:MXOnly-1U-Hotswap |  |  |  | 
| SW35, SW37 | 2 | 0 | SW_PUSH-_reviung-kbd | _reviung-kbd:MXOnly-1U-Hotswap |  |  |  | 
| SW36 | 1 | I | SW_PUSH-_reviung-kbd | _reviung-kbd:MXOnly-1U-Hotswap |  |  |  | 
| SW38 | 1 | P | SW_PUSH-_reviung-kbd | _reviung-kbd:MXOnly-1U-Hotswap |  |  |  | 
| SW40 | 1 | K | SW_PUSH-_reviung-kbd | _reviung-kbd:MXOnly-1U-Hotswap |  |  |  | 
| SW41 | 1 | L | SW_PUSH-_reviung-kbd | _reviung-kbd:MXOnly-1U-Hotswap |  |  |  | 
| SW42, SW46 | 2 | 1U | SW_PUSH-_reviung-kbd | _reviung-kbd:MXOnly-1U-Hotswap |  |  |  | 
| SW45 | 1 | < | SW_PUSH-_reviung-kbd | _reviung-kbd:MXOnly-1U-Hotswap |  |  |  | 
| SW47 | 1 | 2.75U | SW_PUSH-_reviung-kbd | _reviung-kbd:MXOnly-2.75U-Hotswap-ReversedStabilizers |  |  |  | 
| SW52 | 1 | 2.75U | SW_PUSH-_reviung-kbd | _reviung-kbd:MXOnly-2.75U-Hotswap |  |  |  | 
| SW53 | 1 | 6.25U | SW_PUSH-_reviung-kbd | _reviung-kbd:MXOnly-6.25U-Hotswap-ReversedStabilizers |  |  |  | 
| SW54 | 1 | 2.25U | SW_PUSH-_reviung-kbd | _reviung-kbd:MXOnly-2.25U-Hotswap |  |  |  | 
| U1 | 1 | ProMicro | ProMicro-_reviung-kbd | _reviung-kbd:ProMicro |  |  |  |

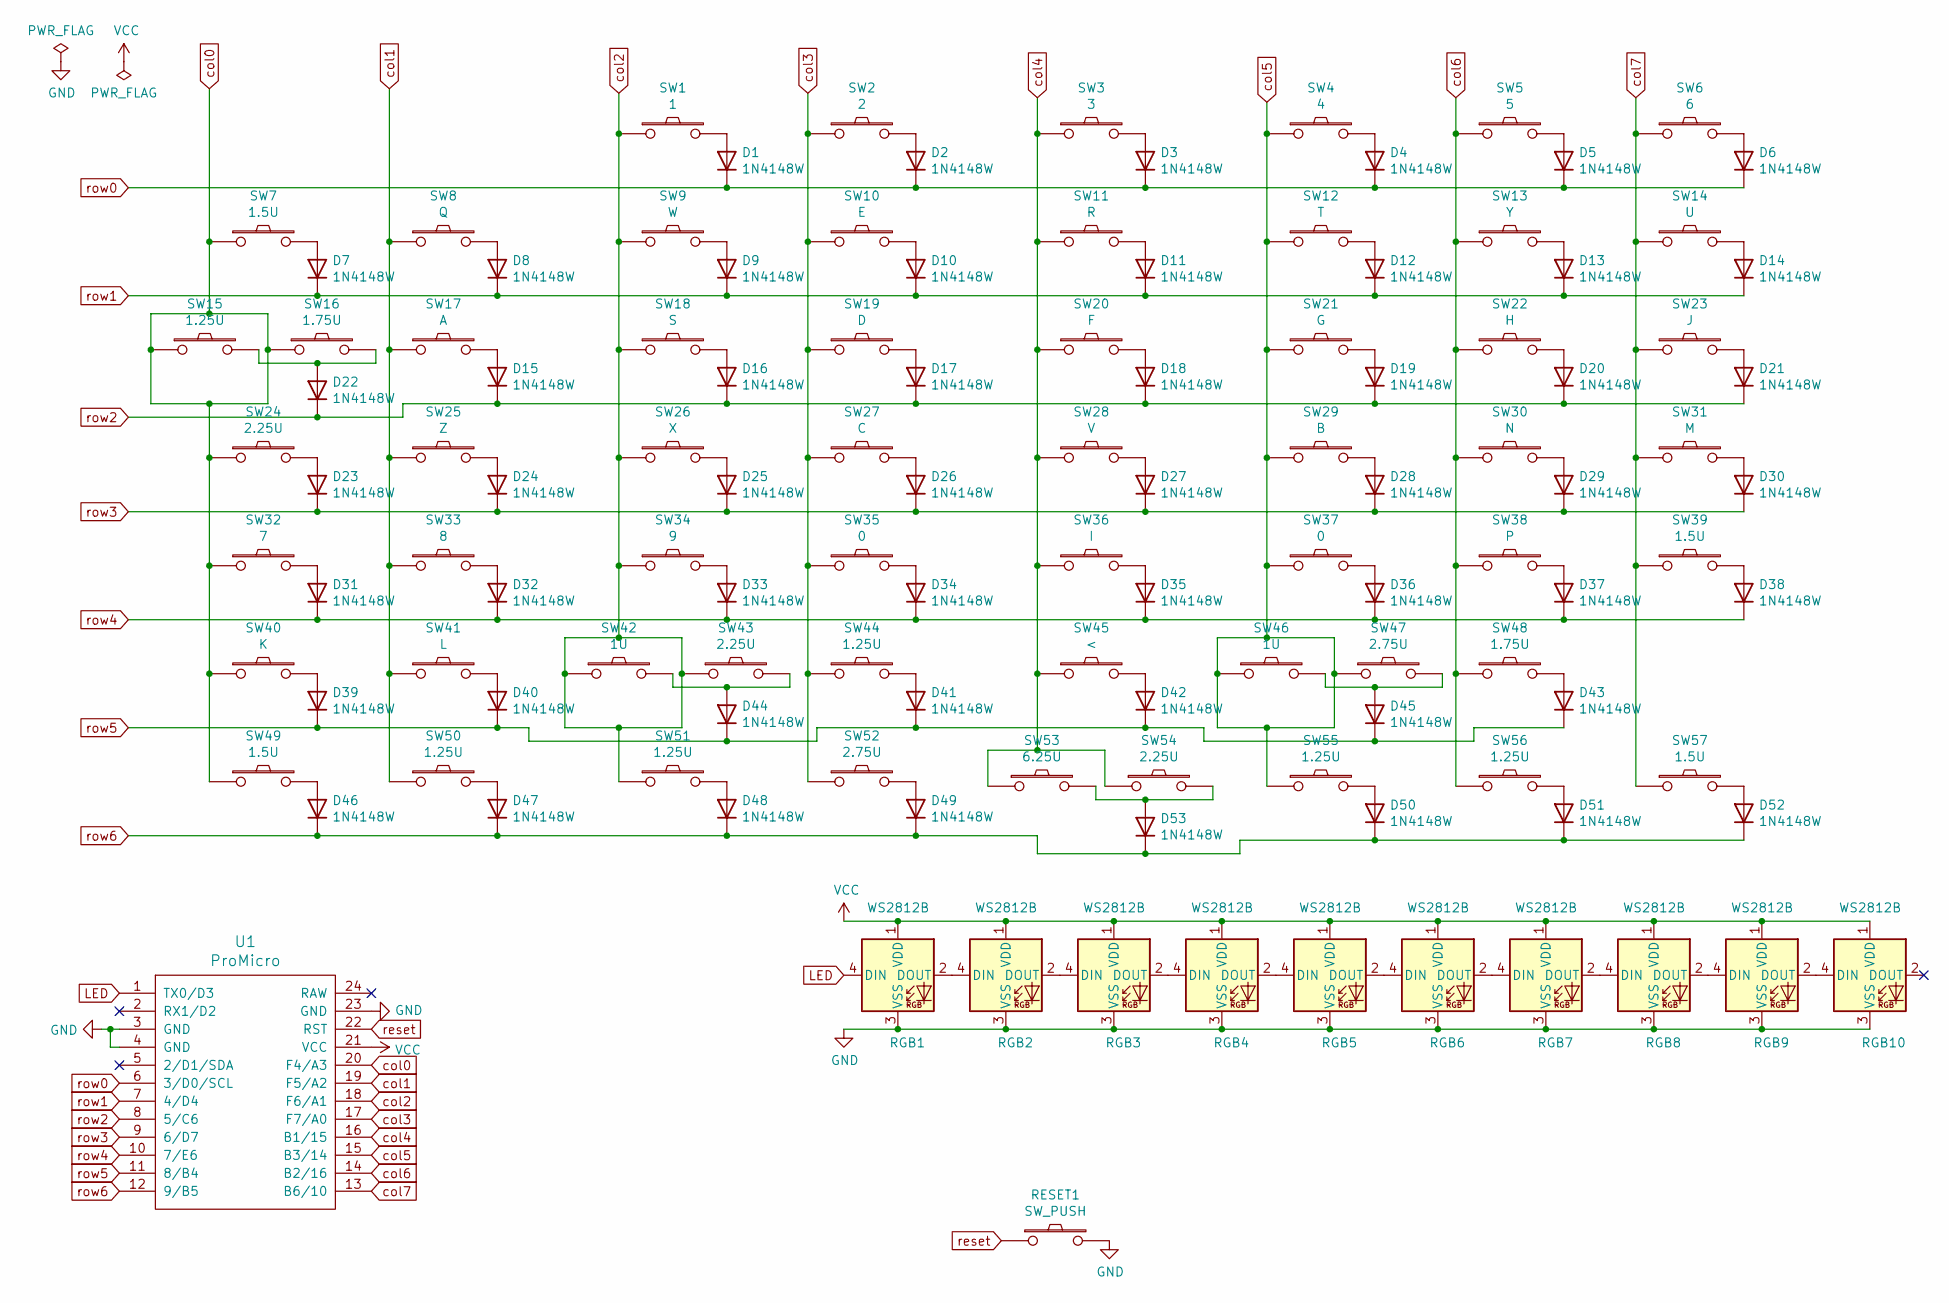
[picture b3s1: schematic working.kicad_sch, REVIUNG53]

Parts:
D1, D2, D3, D4, D5, D6, D7, D8, D9, D10, D11, D12, D13, D14, D15, D16, D17, D18, D19, D20, D21, D22, D23, D24, D25, D26, D27, D28, D29, D30, D31, D32, D33, D34, D35, D36, D37, D38, D39, D40, D41, D42, D43, D44, D45, D46, D47, D48, D49, D50, D51, D52, D53: 1N4148W; D3_SMD_1side
RESET1: SW_PUSH; ResetSW_1side
RGB1, RGB2, RGB3, RGB4, RGB5, RGB6, RGB7, RGB8, RGB9, RGB10: WS2812B; LED_WS2812B_PLCC4_5.0x5.0mm_P3.2mm_BigFoot
SW1: 1; MXOnly-1U-Hotswap
SW2: 2; MXOnly-1U-Hotswap
SW3: 3; MXOnly-1U-Hotswap
SW4: 4; MXOnly-1U-Hotswap
SW5: 5; MXOnly-1U-Hotswap
SW6: 6; MXOnly-1U-Hotswap
SW7, SW39, SW49, SW57: 1.5U; MXOnly-1.5U-Hotswap
SW8: Q; MXOnly-1U-Hotswap
SW9: W; MXOnly-1U-Hotswap
SW10: E; MXOnly-1U-Hotswap
SW11: R; MXOnly-1U-Hotswap
SW12: T; MXOnly-1U-Hotswap
SW13: Y; MXOnly-1U-Hotswap
SW14: U; MXOnly-1U-Hotswap
SW15, SW44, SW50, SW51, SW55, SW56: 1.25U; MXOnly-1.25U-Hotswap
SW16, SW48: 1.75U; MXOnly-1.75U-Hotswap
SW17: A; MXOnly-1U-Hotswap
SW18: S; MXOnly-1U-Hotswap
SW19: D; MXOnly-1U-Hotswap
SW20: F; MXOnly-1U-Hotswap
SW21: G; MXOnly-1U-Hotswap
SW22: H; MXOnly-1U-Hotswap
SW23: J; MXOnly-1U-Hotswap
SW24, SW43: 2.25U; MXOnly-2.25U-Hotswap-ReversedStabilizers
SW25: Z; MXOnly-1U-Hotswap
SW26: X; MXOnly-1U-Hotswap
SW27: C; MXOnly-1U-Hotswap
SW28: V; MXOnly-1U-Hotswap
SW29: B; MXOnly-1U-Hotswap
SW30: N; MXOnly-1U-Hotswap
SW31: M; MXOnly-1U-Hotswap
SW32: 7; MXOnly-1U-Hotswap
SW33: 8; MXOnly-1U-Hotswap
SW34: 9; MXOnly-1U-Hotswap
SW35, SW37: 0; MXOnly-1U-Hotswap
SW36: I; MXOnly-1U-Hotswap
SW38: P; MXOnly-1U-Hotswap
SW40: K; MXOnly-1U-Hotswap
SW41: L; MXOnly-1U-Hotswap
SW42, SW46: 1U; MXOnly-1U-Hotswap
SW45: <; MXOnly-1U-Hotswap
SW47: 2.75U; MXOnly-2.75U-Hotswap-ReversedStabilizers
SW52: 2.75U; MXOnly-2.75U-Hotswap
SW53: 6.25U; MXOnly-6.25U-Hotswap-ReversedStabilizers
SW54: 2.25U; MXOnly-2.25U-Hotswap
U1: ProMicro

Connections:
GND: RESET1.2, RGB1.3 (VSS), RGB2.3 (VSS), RGB3.3 (VSS), RGB4.3 (VSS), RGB5.3 (VSS), RGB6.3 (VSS), RGB7.3 (VSS), RGB8.3 (VSS), RGB9.3 (VSS), RGB10.3 (VSS), U1.3 (GND), U1.4 (GND), U1.23 (GND)
LED: RGB1.4 (DIN), U1.1 (TX0/D3)
unnamed: D1.2 (A), SW1.2
unnamed: D2.2 (A), SW2.2
unnamed: D3.2 (A), SW3.2
unnamed: D4.2 (A), SW4.2
unnamed: D5.2 (A), SW5.2
unnamed: D6.2 (A), SW6.2
unnamed: D7.2 (A), SW7.2
unnamed: D8.2 (A), SW8.2
unnamed: D9.2 (A), SW9.2
unnamed: D10.2 (A), SW10.2
unnamed: D11.2 (A), SW11.2
unnamed: D12.2 (A), SW12.2
unnamed: D13.2 (A), SW13.2
unnamed: D14.2 (A), SW14.2
unnamed: D15.2 (A), SW17.2
unnamed: D16.2 (A), SW18.2
unnamed: D17.2 (A), SW19.2
unnamed: D18.2 (A), SW20.2
unnamed: D19.2 (A), SW21.2
unnamed: D20.2 (A), SW22.2
unnamed: D21.2 (A), SW23.2
unnamed: D22.2 (A), SW15.2, SW16.2
unnamed: D23.2 (A), SW24.2
unnamed: D24.2 (A), SW25.2
unnamed: D25.2 (A), SW26.2
unnamed: D26.2 (A), SW27.2
unnamed: D27.2 (A), SW28.2
unnamed: D28.2 (A), SW29.2
unnamed: D29.2 (A), SW30.2
unnamed: D30.2 (A), SW31.2
unnamed: D31.2 (A), SW32.2
unnamed: D32.2 (A), SW33.2
unnamed: D33.2 (A), SW34.2
unnamed: D34.2 (A), SW35.2
unnamed: D35.2 (A), SW36.2
unnamed: D36.2 (A), SW37.2
unnamed: D37.2 (A), SW38.2
unnamed: D38.2 (A), SW39.2
unnamed: D39.2 (A), SW40.2
unnamed: D40.2 (A), SW41.2
unnamed: D41.2 (A), SW44.2
unnamed: D42.2 (A), SW45.2
unnamed: D43.2 (A), SW48.2
unnamed: D44.2 (A), SW42.2, SW43.2
unnamed: D45.2 (A), SW46.2, SW47.2
unnamed: D46.2 (A), SW49.2
unnamed: D47.2 (A), SW50.2
unnamed: D48.2 (A), SW51.2
unnamed: D49.2 (A), SW52.2
unnamed: D50.2 (A), SW55.2
unnamed: D51.2 (A), SW56.2
unnamed: D52.2 (A), SW57.2
unnamed: D53.2 (A), SW53.2, SW54.2
unnamed: RGB1.2 (DOUT), RGB2.4 (DIN)
unnamed: RGB2.2 (DOUT), RGB3.4 (DIN)
unnamed: RGB3.2 (DOUT), RGB4.4 (DIN)
unnamed: RGB4.2 (DOUT), RGB5.4 (DIN)
unnamed: RGB5.2 (DOUT), RGB6.4 (DIN)
unnamed: RGB6.2 (DOUT), RGB7.4 (DIN)
unnamed: RGB7.2 (DOUT), RGB8.4 (DIN)
unnamed: RGB8.2 (DOUT), RGB9.4 (DIN)
unnamed: RGB9.2 (DOUT), RGB10.4 (DIN)
VCC: RGB1.1 (VDD), RGB2.1 (VDD), RGB3.1 (VDD), RGB4.1 (VDD), RGB5.1 (VDD), RGB6.1 (VDD), RGB7.1 (VDD), RGB8.1 (VDD), RGB9.1 (VDD), RGB10.1 (VDD), U1.21 (VCC)
col0: SW7.1, SW15.1, SW16.1, SW24.1, SW32.1, SW40.1, SW49.1, U1.20 (F4/A3)
col1: SW8.1, SW17.1, SW25.1, SW33.1, SW41.1, SW50.1, U1.19 (F5/A2)
col2: SW1.1, SW9.1, SW18.1, SW26.1, SW34.1, SW42.1, SW43.1, SW51.1, U1.18 (F6/A1)
col3: SW2.1, SW10.1, SW19.1, SW27.1, SW35.1, SW44.1, SW52.1, U1.17 (F7/A0)
col4: SW3.1, SW11.1, SW20.1, SW28.1, SW36.1, SW45.1, SW53.1, SW54.1, U1.16 (B1/15)
col5: SW4.1, SW12.1, SW21.1, SW29.1, SW37.1, SW46.1, SW47.1, SW55.1, U1.15 (B3/14)
col6: SW5.1, SW13.1, SW22.1, SW30.1, SW38.1, SW48.1, SW56.1, U1.14 (B2/16)
col7: SW6.1, SW14.1, SW23.1, SW31.1, SW39.1, SW57.1, U1.13 (B6/10)
reset: RESET1.1, U1.22 (RST)
row0: D1.1 (K), D2.1 (K), D3.1 (K), D4.1 (K), D5.1 (K), D6.1 (K), U1.6 (3/D0/SCL)
row1: D7.1 (K), D8.1 (K), D9.1 (K), D10.1 (K), D11.1 (K), D12.1 (K), D13.1 (K), D14.1 (K), U1.7 (4/D4)
row2: D15.1 (K), D16.1 (K), D17.1 (K), D18.1 (K), D19.1 (K), D20.1 (K), D21.1 (K), D22.1 (K), U1.8 (5/C6)
row3: D23.1 (K), D24.1 (K), D25.1 (K), D26.1 (K), D27.1 (K), D28.1 (K), D29.1 (K), D30.1 (K), U1.9 (6/D7)
row4: D31.1 (K), D32.1 (K), D33.1 (K), D34.1 (K), D35.1 (K), D36.1 (K), D37.1 (K), D38.1 (K), U1.10 (7/E6)
row5: D39.1 (K), D40.1 (K), D41.1 (K), D42.1 (K), D43.1 (K), D44.1 (K), D45.1 (K), U1.11 (8/B4)
row6: D46.1 (K), D47.1 (K), D48.1 (K), D49.1 (K), D50.1 (K), D51.1 (K), D52.1 (K), D53.1 (K), U1.12 (9/B5)
